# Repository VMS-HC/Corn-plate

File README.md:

<div align='center'>

<h1>Hotplate</h1>
<p>Just a simple..ish hot plate that can get up to 250C!</p>

<h4> <a href=https://github.com/VMS-HC/Corn-plate>View Demo</a> <span> · </span> <a href="https://github.com/Bobert3D/Corn-plate/blob/master/README.md"> Documentation </a> <span> · </span> <a href="https://github.com/VMS-HC/Corn-plate/issues?q=sort%3Aupdated-desc+is%3Aissue+state%3Aopen+"> Report Bug </a> <span> · </span> <a href="https://github.com/VMS-HC/Corn-plate/issues?q=sort%3Aupdated-desc+is%3Aissue+state%3Aopen+"> Request Feature </a> </h4>

</div>

# Table of Contents

- [About the Project](#star2-about-the-project)
- [Roadmap](#compass-roadmap)
- [FAQ](#grey_question-faq)
- [License](#warning-license)
- [Contact](#handshake-author)
- [Acknowledgements](#gem-acknowledgements)

## :star2: About the Project

### :dart: Features
- Reflow plate
- Soldering hotplate
- Hotplate
- Reflow Soldering

### :art: Color Reference
| Color | Hex |
| --------------- | ---------------------------------------------------------------- |
| Primary Color |  #179a73 |
| Secondary Color |  #190973 |
| Accent Color |  #07787e |
| Text Color |  #067fa0 |

## :toolbox: Getting Started

### :bangbang: Prerequisites

- Kicad<a href="kicad.org"> Here</a>
```bash
sudo add-apt-repository --yes ppa:kicad/kicad-10.0-releases sudo apt update sudo apt install --install-recommends kicad
```

### :gear: Installation

Kicad
```bash
sudo add-apt-repository --yes ppa:kicad/kicad-10.0-releases sudo apt update sudo apt install --install-recommends kicad
```

### :test_tube: Running Tests

Kicad-files
```bash
kicad
```

### :running: Run Locally

Clone the project

```bash
https://github.com/VMS-HC/Corn-Bit
```
Clone
```bash
git clone https://github.com/VMS-HC/Corn-plate
```
Kicad
```bash
sudo apt install kicad
```
cd
```bash
cd ~/Corn-plate
```

### :triangular_flag_on_post: Deployment

Kicad
```bash
kicad
```

## :compass: Roadmap

* [x] First wrecked pcb
* [x] Final version
* [ ] Continuous revisions
* [x] Cry

## :grey_question: FAQ

- Is this a beginner project?
- NO! But I won't stop you! This has high voltage and amperage and complex boards!
- Can I copy this?
- Well. Yes and no just make sure to follow the MIT Licence!

## :warning: License

Distributed under the MIT License. See LICENSE.txt for more information.

## :handshake: author

Bobert3D 

Project Link: [https://github.com/VMS-HC/Corn-Bit](https://github.com/VMS-HC/Corn-Bit)

## :gem: Acknowledgements

Use this section to mention useful resources and libraries that you have used in your projects.

- [Thanks to all the Hack Club staff and especially Rudy at Fabricate YSWS!](Kicad docs and Hack Club)

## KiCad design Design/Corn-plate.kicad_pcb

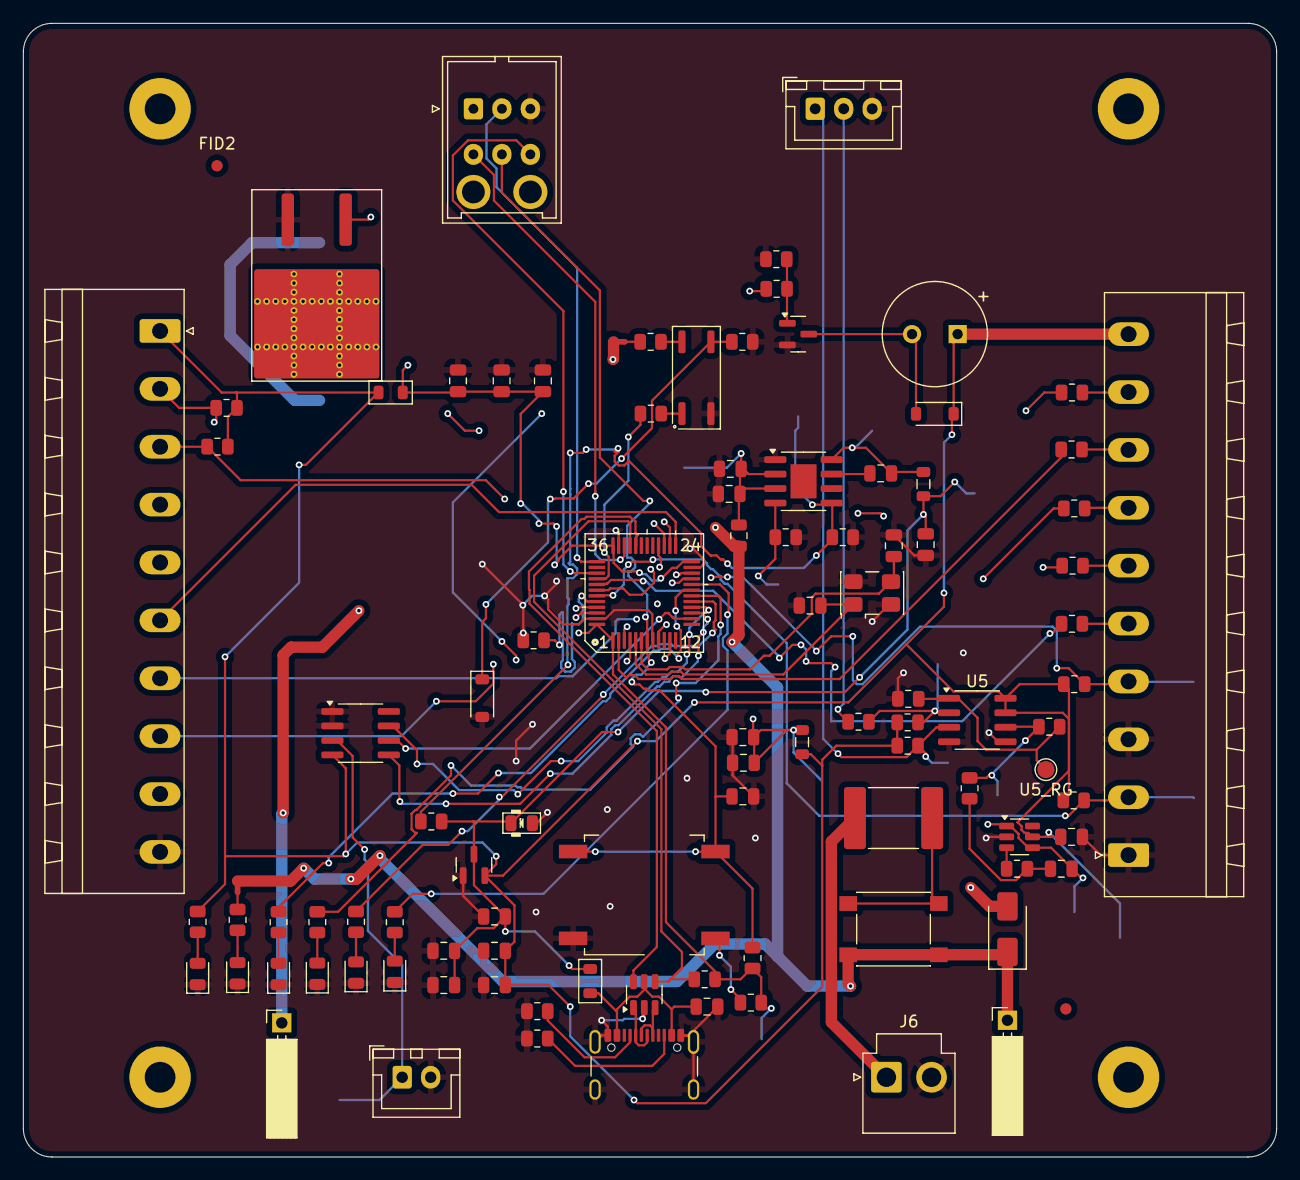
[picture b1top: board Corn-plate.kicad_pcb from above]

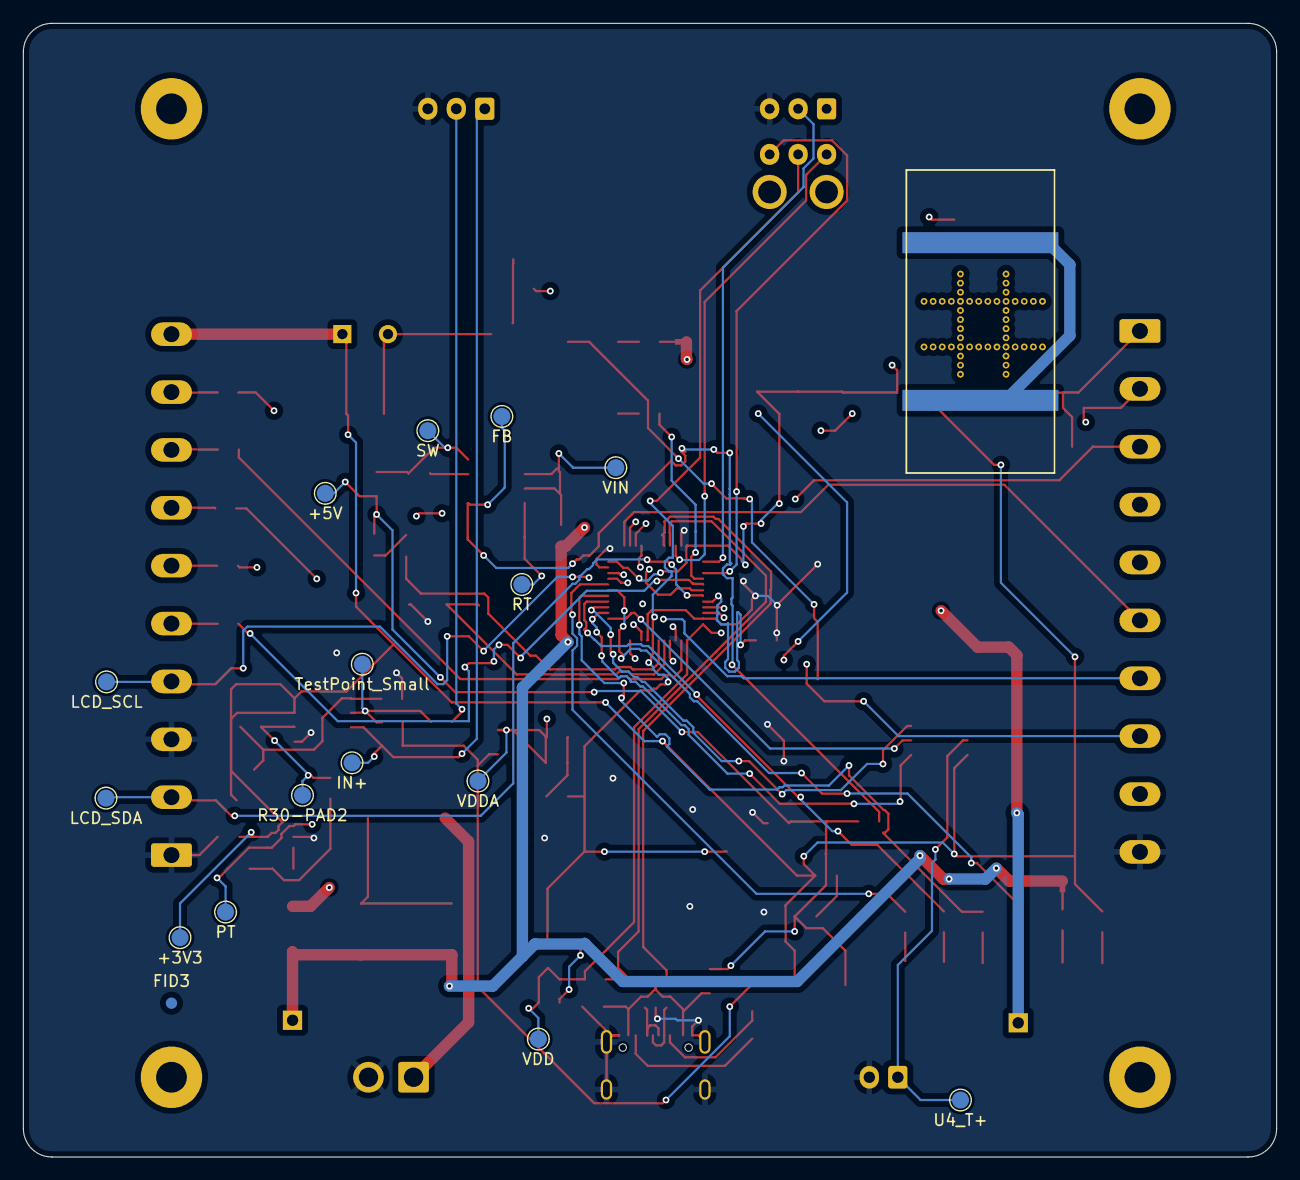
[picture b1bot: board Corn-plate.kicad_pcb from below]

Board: 4 copper layers, 110.0 x 99.5 mm, 121 parts (17 on the bottom side), 78 nets.

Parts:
BZ1: Buzzer; MagneticBuzzer_CUI_CST-931RP-A
C1, C4, C5, C6, C7, C10, C11, C15, C16, C18, C19, C20: 100nF; C_0805_2012Metric
C2, C3: 10pF; C_0805_2012Metric
C8: 1uF; C_0805_2012Metric
C9: 4u7; C_0805_2012Metric
C12, C13: 22nF; C_0805_2012Metric
C14, C17: 1u; C_0805_2012Metric
D1: 15V; D_SOD-123
D2: SKL310; D_SMA
D3, D4: GREEN; LED_0805_2012Metric
D5, D7, D8, D9: YELLOW; LED_0805_2012Metric
D6: MBR1020VL; D_SOD-123
D10: 1u; D_0805_2012Metric_Zener
F1: 500mA; Fuse_0805_2012Metric
F2: 10A; Fuse_2920_7451Metric
FB1, FB2: 470R; Ferrite_0805_2012Metric
FID1, FID2, FID3: Fiducial; Fiducial_1mm_Mask2mm
H1, H2, H3, H4: 2.5mm; MountingHole_2.7mm_M2.5_Pad
HS1: Heatsink_Pad_2Pin; Heatsink_AAVID_573300D00010G_TO-263
J1: SWD; JST_J2100_B06B-J21DK-GGXR_2x03_P2.50x4.00mm_Vertical
J2: AUX; PhoenixContact_MSTBA_2,5_10-G-5,08_1x10_P5.08mm_Horizontal
J3: PANEL; PhoenixContact_MSTBA_2,5_10-G-5,08_1x10_P5.08mm_Horizontal
J4, J5: Conn_01x01; PinSocket_1x01_P2.54mm_Horizontal
J6: 6.5/2mm; JST_VH_B2P-VH_1x02_P3.96mm_Vertical
J7: JST_03; JST_XH_B3B-XH-A_1x03_P2.50mm_Vertical
J8: JST_02; JST_XH_B2B-XH-A_1x02_P2.50mm_Vertical
J9: USB_C_Receptacle_USB2.0_16P; USB_C_Receptacle_GCT_USB4105-xx-A_16P_TopMnt_Horizontal
L1: 10uH; L_0805_2012Metric
L2: 15u; L_0805_2012Metric
NT1, NT2: NetTie_2; NetTie-2_SMD_Pad0.5mm
OC1: TLP183; SO-4_4.4x3.6mm_P2.54mm
Q1: IRF1018ES; TO-263-2_ThermalVias2
Q2: 2N7002AQ; SOT-23
R1: 330R; R_0805_2012Metric
R2, R3, R4, R5, R6, R7, R20: 10k; R_0805_2012Metric
R8, R9, R10, R11, R13, R18, R29: 100R; R_0805_2012Metric
R12: 270R; R_0805_2012Metric
R14, R15, R27, R28, R31: 1k; R_0805_2012Metric
R16: 2k2; R_0805_2012Metric
R17, R19, R21, R22, R23: 120R; R_0805_2012Metric
R24: 25k5; R_0805_2012Metric
R25, R26: 100k; R_0805_2012Metric
R30: 4k99; R_0805_2012Metric
R32, R33: 3k3; R_0805_2012Metric
R34: 1k47; R_0805_2012Metric
R35, R36: 5k1; R_0805_2012Metric
SW1: SW_MEC_5G_2LED; SW_MEC_5GSH9
SW2: SW_SPST_Lamp; SW_SPST_PTS645
TP1: VDD; TestPoint_Pad_D1.5mm
TP2: VDDA; TestPoint_Pad_D1.5mm
TP3: LCD_SCL; TestPoint_Pad_D1.5mm
TP4: LCD_SDA; TestPoint_Pad_D1.5mm
TP5: RT; TestPoint_Pad_D1.5mm
TP6: VIN; TestPoint_Pad_D1.5mm
TP7: SW; TestPoint_Pad_D1.5mm
TP8: FB; TestPoint_Pad_D1.5mm
TP9: +5V; TestPoint_Pad_D1.5mm
TP10: +3V3; TestPoint_Pad_D1.5mm
TP11: IN+; TestPoint_Pad_D1.5mm
TP12: TestPoint_Small; TestPoint_Pad_D1.5mm
TP13: U4_T+; TestPoint_Pad_D1.5mm
TP14: R30-PAD2; TestPoint_Pad_D1.5mm
TP15: U5_RG; TestPoint_Pad_D1.5mm
TP16: PT; TestPoint_Pad_D1.5mm
U1: STM32F103CBTx; LQFP-48_7x7mm_P0.5mm
U2: LMR38010SDDAR; SOIC-8-1EP_3.9x4.9mm_P1.27mm_EP2.29x3mm
U3: TLV76133DCY; SOT-23
U4: MAX6675ISA+; SOIC-8_3.9x4.9mm_P1.27mm
U5: MCP6N11T-005E-SN; SOIC-8_3.9x4.9mm_P1.27mm
U6: MCP6001T-I-OT; SOT-23-6
U7: USBLC6-2SC6; SOT-23-6
Y1: Crystal_GND24; Crystal_SMD_5032-4Pin_5.0x3.2mm

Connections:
+3V3: BZ1.1 (+), C16.2, C17.2, C18.1, D6.1 (K), FB1.1, J2.1, J3.10, L1.1, R4.2, R5.2, R6.2, R7.2, R17.1, R27.2, R28.2, TP10.1, U3.2 (VO), U4.4 (VCC), U5.7 (V+), U5.8 (EN/~CAL), U6.5 (V+)
+5V: C12.2, C13.2, C14.2, C15.2, D10.1 (K), FB2.1, L2.2, R25.1, TP9.1, U3.3 (VI)
+24V: D2.1 (K), F1.1, J4.1, NT1.2, NT2.2, SW2.2
/BUTTON_DOWN: R8.1, U1.3 (PC14)
/BUTTON_LEFT: R11.1, U1.45 (PB8)
/BUTTON_RIGHT: R10.1, U1.46 (PB9)
/BUTTON_UP: R9.1, U1.2 (PC13)
/BUZZER: R18.1, U1.4 (PC15)
/HEATBED: R13.1, U1.40 (PB4)
/HSE_IN: C2.2, U1.5 (PD0), Y1.1
/HSE_OUT: C3.2, U1.6 (PD1), Y1.3
/I2C2_SCL: J2.2, R4.1, U1.21 (PB10)
/I2C2_SDA: J2.3, R5.1, U1.22 (PB11)
/LCD_SCL: J3.4, R6.1, TP3.1, U1.42 (PB6)
/LCD_SDA: J3.2, R7.1, TP4.1, U1.43 (PB7)
/LED_COOLING: R23.1, U1.20 (PB2)
/LED_PREHEAT: R19.1, U1.17 (PA7)
/LED_REFLOW: R22.1, U1.19 (PB1)
/LED_SOAK: R21.1, U1.18 (PB0)
/LED_STATUS: R12.1, U1.41 (PB5)
/NRST: C6.2, J1.5, R2.1, SW1.3 (K), SW1.4 (A), U1.7 (NRST)
/PT: C19.2, TP16.1, U1.11 (PA1), U6.1, U6.4 (-)
/Power Supply/FB: R25.2, R26.1, TP8.1, U2.5 (FB)
/Power Supply/RT: R24.1, TP5.1, U2.4 (RT_SYNC)
/Power Supply/SW: C11.2, L2.1, TP7.1, U2.8 (SW)
/Power Supply/VIN: C9.1, C10.1, F1.2, TP6.1, U2.2 (EN), U2.3 (VIN)
/SPI2_MISO: J2.7, U1.27 (PB14)
/SPI2_MOSI: J2.9, U1.28 (PB15)
/SPI2_SCK: J2.8, U1.26 (PB13)
/SPI2_~CS: J2.6, U1.25 (PB12)
/SWCLK: J1.2, U1.37 (PA14)
/SWDIO: J1.4, U1.34 (PA13)
/SWO: J1.6, U1.39 (PB3)
/TS_SCK: U1.15 (PA5), U4.5 (SCK)
/TS_SO: U1.16 (PA6), U4.7 (SO)
/TS_~CS: U1.14 (PA4), U4.6 (~CS)
/Temperature Sensors/IN+: J7.1, R27.1, TP11.1, U5.3 (+)
/Temperature Sensors/IN-: R28.1, R29.2, TP12.1, U5.2 (-)
/USB Connector/DATA+: J9.A6 (D+), J9.B6 (D+), U7.3 (I/O2)
/USB Connector/DATA-: J9.A7 (D-), J9.B7 (D-), U7.1 (I/O1)
/USB Connector/VBUS: C20.1, FB2.2, J9.A4 (VBUS), J9.A9 (VBUS), J9.B4 (VBUS), J9.B9 (VBUS), U7.5 (VBUS)
/USB_D+: R34.1, U1.33 (PA12), U7.4 (I/O2)
/USB_D-: U1.32 (PA11), U7.6 (I/O1)
GND: C1.1, C2.1, C3.1, C4.1, C5.1, C6.1, C7.1, C8.1, C9.2, C10.2, C12.1, C13.1, C14.1, C15.1, C16.1, C17.1, C18.2, C20.2, D1.2 (A), D3.1 (K), D4.1 (K), D5.1 (K), D7.1 (K), D8.1 (K), D9.1 (K), D10.2 (A), J1.3, J2.10, J3.1, J3.3, J6.2, J7.3, J8.2, J9.A1 (GND), J9.A12 (GND), J9.B1 (GND), J9.B12 (GND), J9.S1 (SHIELD), OC1.2, Q1.3 (S), Q2.2 (S), R3.1, R15.1, R20.1, R24.2, R26.2, R31.1, R35.2, R36.2, SW1.1, U1.8 (VSSA), U1.23 (VSS), U1.35 (VSS), U1.47 (VSS), U2.1 (GND), U3.1 (GND), U4.1 (GND), U4.2 (T-), U5.4 (V-), U5.5 (REF), U6.2 (V-), U7.2 (GND), Y1.2, Y1.4
unnamed: BZ1.2 (-), D6.2 (A), Q2.3 (D)
unnamed: C19.1, R32.1, R33.2
unnamed: D1.1 (K), OC1.3, Q1.1 (G), R15.2
unnamed: D2.2 (A), J5.1, Q1.2 (D)
unnamed: D3.2 (A), R16.2
unnamed: D4.2 (A), R17.2
unnamed: D5.2 (A), R19.2
unnamed: D7.2 (A), R21.2
unnamed: D8.2 (A), R22.2
unnamed: D9.2 (A), R23.2
unnamed: F2.1, J6.1
unnamed: F2.2, SW2.1
unnamed: J3.5, R12.2
unnamed: J3.6, R11.2
unnamed: J3.7, R10.2
unnamed: J3.8, R9.2
unnamed: J3.9, R8.2
unnamed: J7.2, R29.1
unnamed: J9.A5 (CC1), R35.1
unnamed: J9.B5 (CC2), R36.1
unnamed: NT1.1, R14.2
unnamed: NT2.1, R16.1
unnamed: OC1.1, R13.2
unnamed: OC1.4, R14.1
unnamed: Q2.1 (G), R18.2, R20.2
unnamed: R1.2, SW1.2
unnamed: R30.2, R32.2, TP14.1, U5.6
unnamed: R3.2, U1.44 (BOOT0)
unnamed: C11.1, U2.7 (BOOT)
unnamed: J8.1, TP13.1, U4.3 (T+)
unnamed: R30.1, R31.2, TP15.1, U5.1 (RG)
unnamed: R33.1, U6.3 (+)
VDD: C1.2, C4.2, C5.2, FB1.2, J1.1, R1.1, R2.2, R34.2, TP1.1, U1.1 (VBAT), U1.24 (VDD), U1.36 (VDD), U1.48 (VDD)
VDDA: C7.2, C8.2, L1.2, TP2.1, U1.9 (VDDA)
